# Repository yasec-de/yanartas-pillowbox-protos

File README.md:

# Yanartas Pillowbox Prototype Designs

This repo contains prototype tamper-sensing meshes designed using the [Yanartas Pillowbox
Generator](https://git.yasec.de/yasec/yanartas-pillowbox-generator).

## Repository Contents

### `proto-01-transparent`
**version:** `v1 2026-10-23`

`proto-01-transparent` is the first physical protoype of a generated mesh. This protoype uses two layers with two mesh
segments each for four total segments. Each segment uses two mesh traces for a total of 16 mesh traces across both
layers.

The prototype is designed to be produced using the transparent flexible substrate offered by
[JLCPCB](https://jlcpcb.com). The traces are intentionally laid out without a ground plane and using thin traces with a
very wide spacing so that the finished mesh stays transparent.

License
-------

© 2026 Dr.-Ing. Jan Sebastian 'jaseg' Götte

This project is licensed [CERN-OHL-S v2](https://ohwr.org/cern_ohl_s_v2.txt).

LLM/AI Policy
-------------

This project does not accept LLM-generated contributions.

## Funding

Part of this project is funded by the nlnet [NGI0 Commons Fund](https://nlnet.nl/commonsfund/) as part of the [Yanartas
project](https://nlnet.nl/project/Yanartas/).

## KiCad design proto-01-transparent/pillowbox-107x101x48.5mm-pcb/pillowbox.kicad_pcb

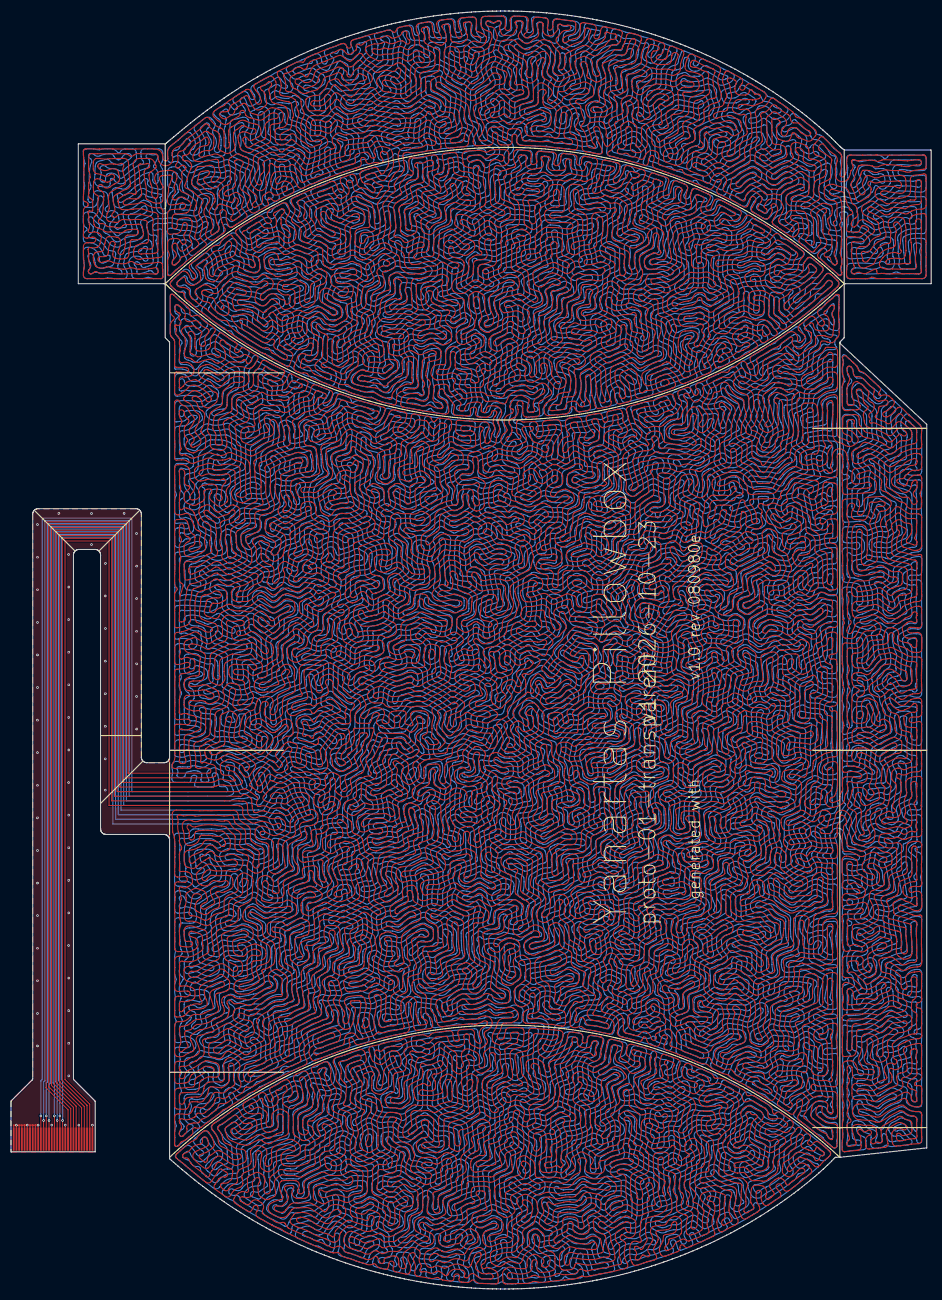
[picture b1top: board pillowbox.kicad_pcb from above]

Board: 2 copper layers, 169.4 x 235.3 mm, 6 parts (0 on the bottom side), 9 nets.

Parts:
BMFTR-Logo_w30.00mm: G*****; BMFTR-Logo_w30.00mm
J1: FPC plug; FPC_plug
PTF-Logo_w30.00mm: G*****; PTF-Logo_w30.00mm
ashen-logo-text_w15.00mm: G*****; ashen-logo-text_w15.00mm
ngi-zero-commons-logo_w35.00mm: G*****; ngi-zero-commons-logo_w35.00mm
nlnet-logo_w25.00mm: G*****; nlnet-logo_w25.00mm

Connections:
GND: J1.1, J1.6, J1.11, J1.16, J1.21, J1.22, J1.23, J1.24, J1.25, J1.26, J1.27, J1.28, J1.29, J1.30
MESH_B1: J1.17, J1.20
MESH_B2: J1.18, J1.19
MESH_B3: J1.12, J1.15
MESH_B4: J1.13, J1.14
MESH_F1: J1.7, J1.10
MESH_F2: J1.8, J1.9
MESH_F3: J1.2, J1.5
MESH_F4: J1.3, J1.4
